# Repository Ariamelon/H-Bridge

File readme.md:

# H-Bridge
A mosfet H-Bridge brushed motor controller created for university. It's easily capable of driving 3A and should be capable of more.

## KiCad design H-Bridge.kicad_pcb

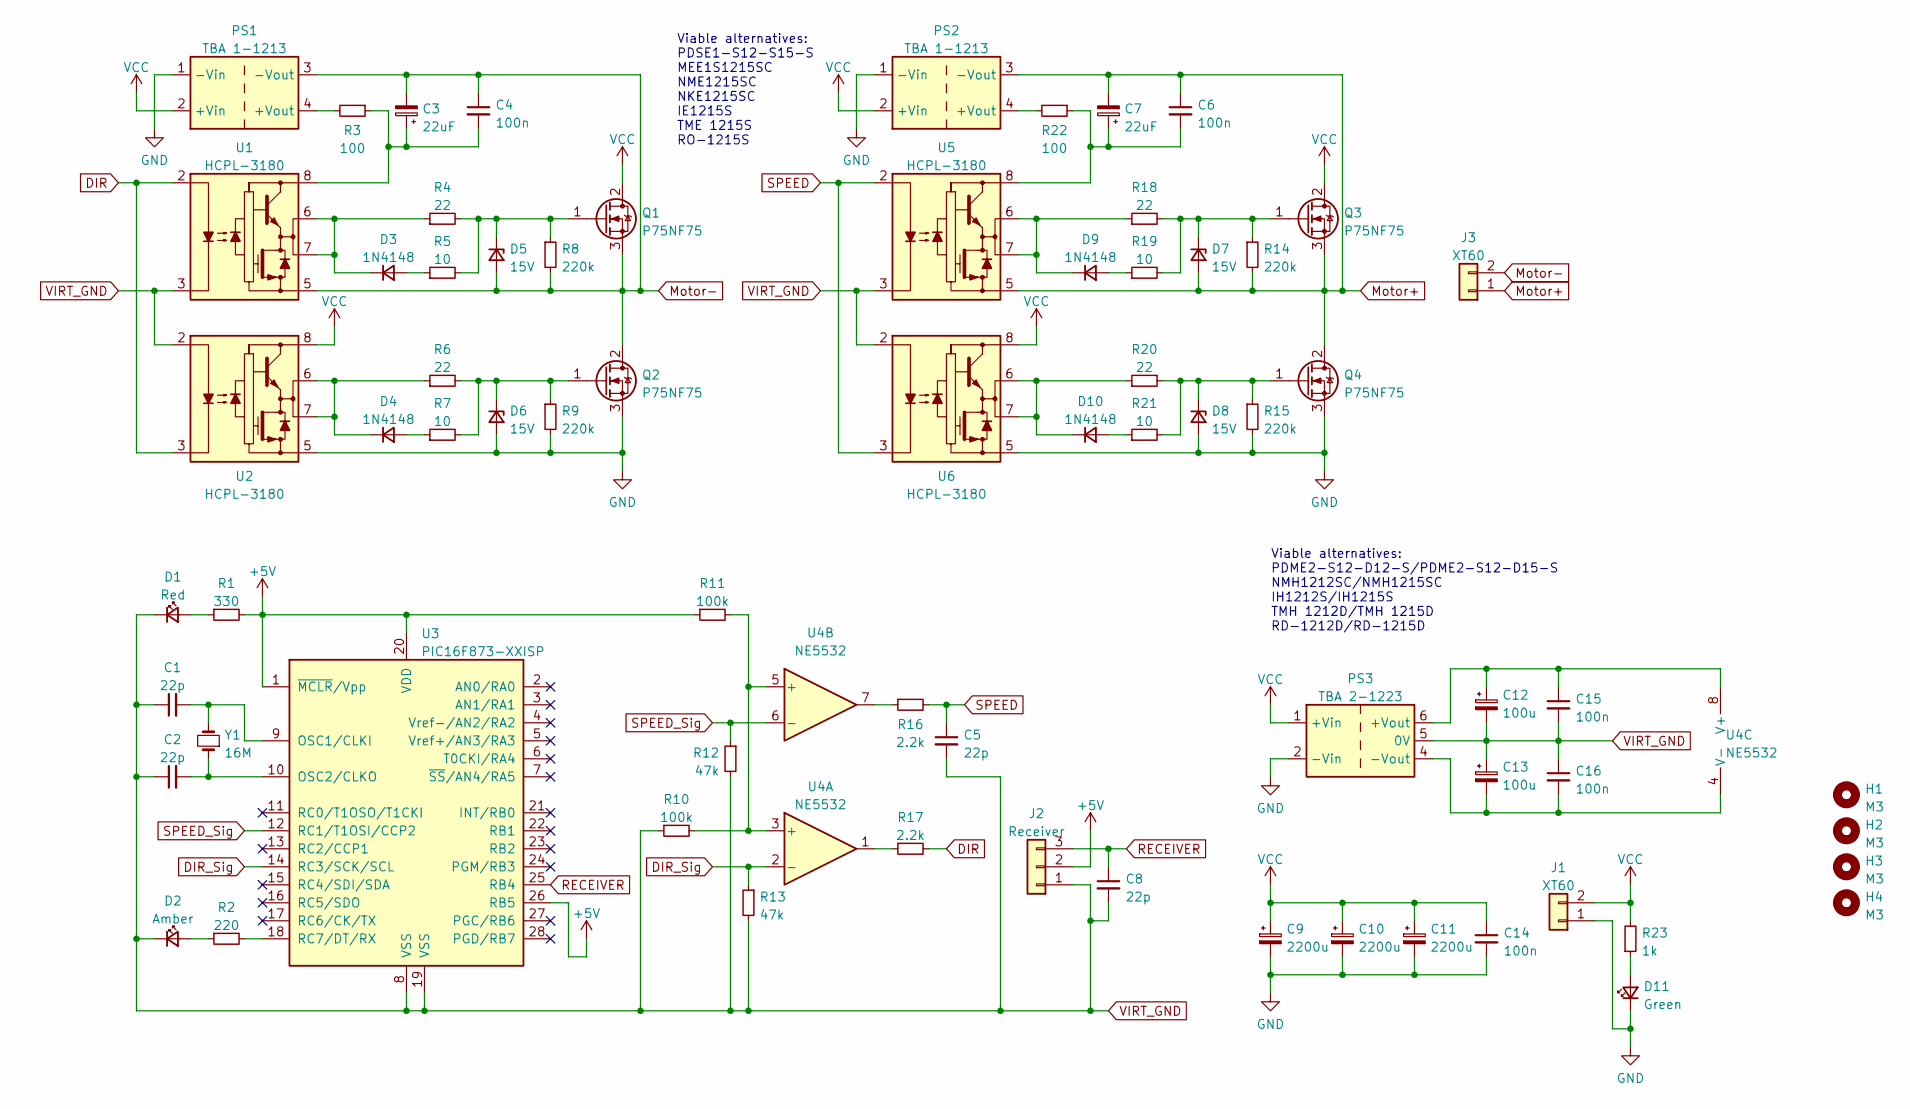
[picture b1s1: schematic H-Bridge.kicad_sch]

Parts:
C1, C2, C5, C8: 22p; C_Disc_D5.0mm_W2.5mm_P2.50mm
C3, C7: 22uF; CP_Radial_D5.0mm_P2.50mm
C4, C6, C14, C15, C16: 100n; C_Disc_D6.0mm_W2.5mm_P5.00mm
C9, C10, C11: 2200u; CP_Radial_D16.0mm_P7.50mm
C12, C13: 100u; CP_Radial_D8.0mm_P3.50mm
D1: Red; LED_D3.0mm
D2: Amber; LED_D3.0mm
D3, D4, D9, D10: 1N4148; D_DO-35_SOD27_P7.62mm_Horizontal
D5, D6, D7, D8: 15V; D_DO-41_SOD81_P7.62mm_Horizontal
D11: Green; LED_D3.0mm
H1, H2, H3, H4: M3; MountingHole_3.2mm_M3_DIN965_Pad
J1, J3: XT60; AMASS_XT60-M
J2: Receiver; PinSocket_1x03_P2.54mm_Vertical
PS1, PS2: TBA 1-1213; Converter_DCDC_Murata_MEE1SxxxxSC_THT
PS3: TBA 2-1223; Converter_DCDC_XP_POWER-IHxxxxS_THT
Q1, Q2, Q3, Q4: P75NF75; TO-220-3_Vertical
R1: 330; R_Axial_DIN0207_L6.3mm_D2.5mm_P7.62mm_Horizontal
R2: 220; R_Axial_DIN0207_L6.3mm_D2.5mm_P7.62mm_Horizontal
R3, R22: 100; R_Axial_DIN0207_L6.3mm_D2.5mm_P7.62mm_Horizontal
R4, R6, R18, R20: 22; R_Axial_DIN0207_L6.3mm_D2.5mm_P7.62mm_Horizontal
R5, R7, R19, R21: 10; R_Axial_DIN0207_L6.3mm_D2.5mm_P7.62mm_Horizontal
R8, R9, R14, R15: 220k; R_Axial_DIN0207_L6.3mm_D2.5mm_P7.62mm_Horizontal
R10, R11: 100k; R_Axial_DIN0207_L6.3mm_D2.5mm_P7.62mm_Horizontal
R12, R13: 47k; R_Axial_DIN0207_L6.3mm_D2.5mm_P7.62mm_Horizontal
R16, R17: 2.2k; R_Axial_DIN0207_L6.3mm_D2.5mm_P7.62mm_Horizontal
R23: 1k; R_Axial_DIN0207_L6.3mm_D2.5mm_P7.62mm_Horizontal
U1, U2, U5, U6: HCPL-3180; DIP-8_W7.62mm_Socket
U3: PIC16F873-XXISP; DIP-28_W7.62mm_Socket
U4: NE5532; DIP-8_W7.62mm_Socket
Y1: 16M; Crystal_HC49-U_Vertical

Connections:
+5V: J2.2, R1.2, R11.1, U3.1 (~MCLR/Vpp), U3.20 (VDD), U3.26 (RB5)
DIR: R17.2, U1.2 (A), U2.3 (C)
DIR_Sig: R13.1, U3.14 (RC3/SCK/SCL), U4.2 (-)
GND: C9.2, C10.2, C11.2, C14.2, D6.2 (A), D8.2 (A), D11.1 (K), J1.1, PS1.1 (-Vin), PS2.1 (-Vin), PS3.2 (-Vin), Q2.3 (S), Q4.3 (S), R9.2, R15.2, U2.5 (VEE), U6.5 (VEE)
Motor+: C6.1, C7.2, D7.2 (A), J3.1, PS2.3 (-Vout), Q3.3 (S), Q4.2 (D), R14.2, U5.5 (VEE)
Motor-: C3.2, C4.1, D5.2 (A), J3.2, PS1.3 (-Vout), Q1.3 (S), Q2.2 (D), R8.2, U1.5 (VEE)
unnamed: C1.2, U3.9 (OSC1/CLKI), Y1.2
unnamed: C2.2, U3.10 (OSC2/CLKO), Y1.1
unnamed: C3.1, C4.2, R3.1, U1.8 (VCC)
unnamed: C6.2, C7.1, R22.1, U5.8 (VCC)
unnamed: C12.1, C15.1, PS3.6 (+Vout), U4.8 (V+)
unnamed: C13.2, C16.2, PS3.4 (-Vout), U4.4 (V-)
unnamed: D1.2 (A), R1.1
unnamed: D2.2 (A), R2.1
unnamed: D3.1 (K), R4.1, U1.6 (VO), U1.7 (VO)
unnamed: D3.2 (A), R5.1
unnamed: D4.1 (K), R6.1, U2.6 (VO), U2.7 (VO)
unnamed: D4.2 (A), R7.1
unnamed: D5.1 (K), Q1.1 (G), R4.2, R5.2, R8.1
unnamed: D6.1 (K), Q2.1 (G), R6.2, R7.2, R9.1
unnamed: D7.1 (K), Q3.1 (G), R14.1, R18.2, R19.2
unnamed: D8.1 (K), Q4.1 (G), R15.1, R20.2, R21.2
unnamed: D9.1 (K), R18.1, U5.6 (VO), U5.7 (VO)
unnamed: D9.2 (A), R19.1
unnamed: D10.1 (K), R20.1, U6.6 (VO), U6.7 (VO)
unnamed: D10.2 (A), R21.1
unnamed: D11.2 (A), R23.1
unnamed: PS1.4 (+Vout), R3.2
unnamed: PS2.4 (+Vout), R22.2
unnamed: R2.2, U3.18 (RC7/DT/RX)
unnamed: R10.2, R11.2, U4.3 (+), U4.5 (+)
unnamed: R16.1, U4.7
unnamed: R17.1, U4.1
RECEIVER: C8.1, J2.3, U3.25 (RB4)
SPEED: C5.1, R16.2, U5.2 (A), U6.3 (C)
SPEED_Sig: R12.1, U3.12 (RC1/T1OSI/CCP2), U4.6 (-)
VCC: C9.1, C10.1, C11.1, C14.1, J1.2, PS1.2 (+Vin), PS2.2 (+Vin), PS3.1 (+Vin), Q1.2 (D), Q3.2 (D), R23.2, U2.8 (VCC), U6.8 (VCC)
VIRT_GND: C1.1, C2.1, C5.2, C8.2, C12.2, C13.1, C15.2, C16.1, D1.1 (K), D2.1 (K), J2.1, PS3.5 (0V), R10.1, R12.2, R13.2, U1.3 (C), U2.2 (A), U3.8 (VSS), U3.19 (VSS), U5.3 (C), U6.2 (A)

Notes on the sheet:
Viable alternatives: PDSE1-S12-S15-S MEE1S1215SC NME1215SC NKE1215SC IE1215S TME 1215S RO-1215S
Viable alternatives: PDME2-S12-D12-S/PDME2-S12-D15-S NMH1212SC/NMH1215SC IH1212S/IH1215S TMH 1212D/TMH 1215D RD-1212D/RD-1215D

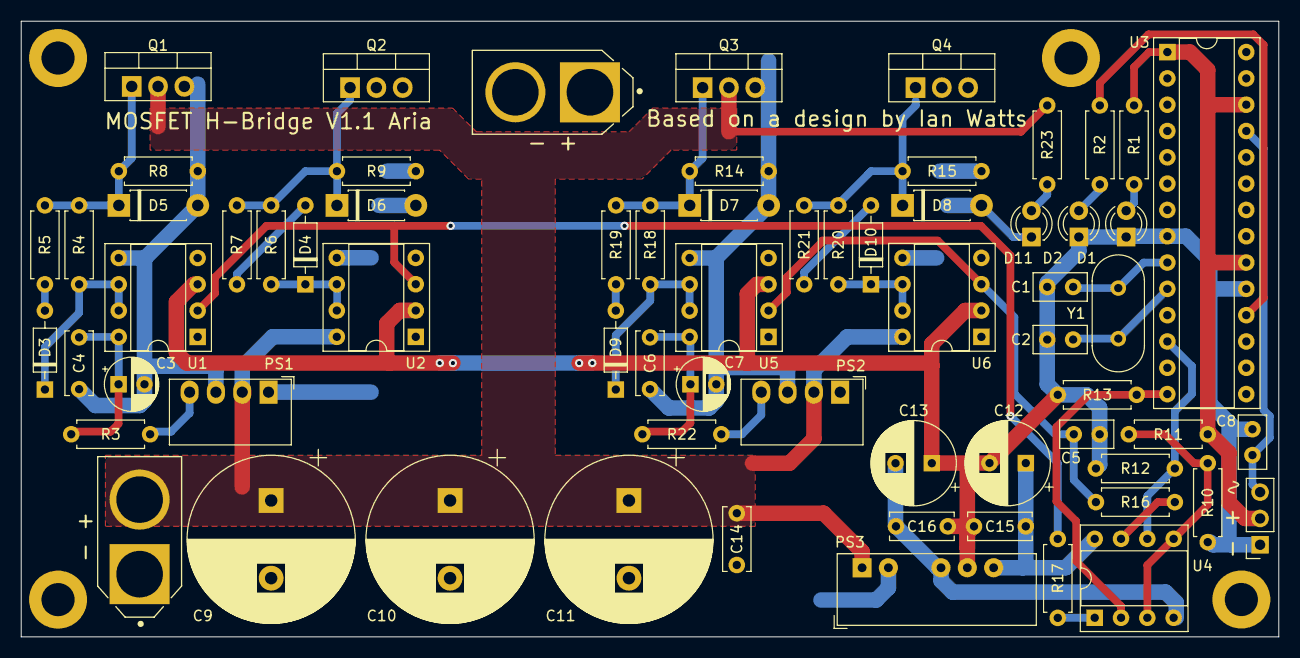
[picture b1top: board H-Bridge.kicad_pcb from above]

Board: 2 copper layers, 121.4 x 59.4 mm, 71 parts (0 on the bottom side), 38 nets.

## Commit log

2023-11-01 Uploaded images and video
